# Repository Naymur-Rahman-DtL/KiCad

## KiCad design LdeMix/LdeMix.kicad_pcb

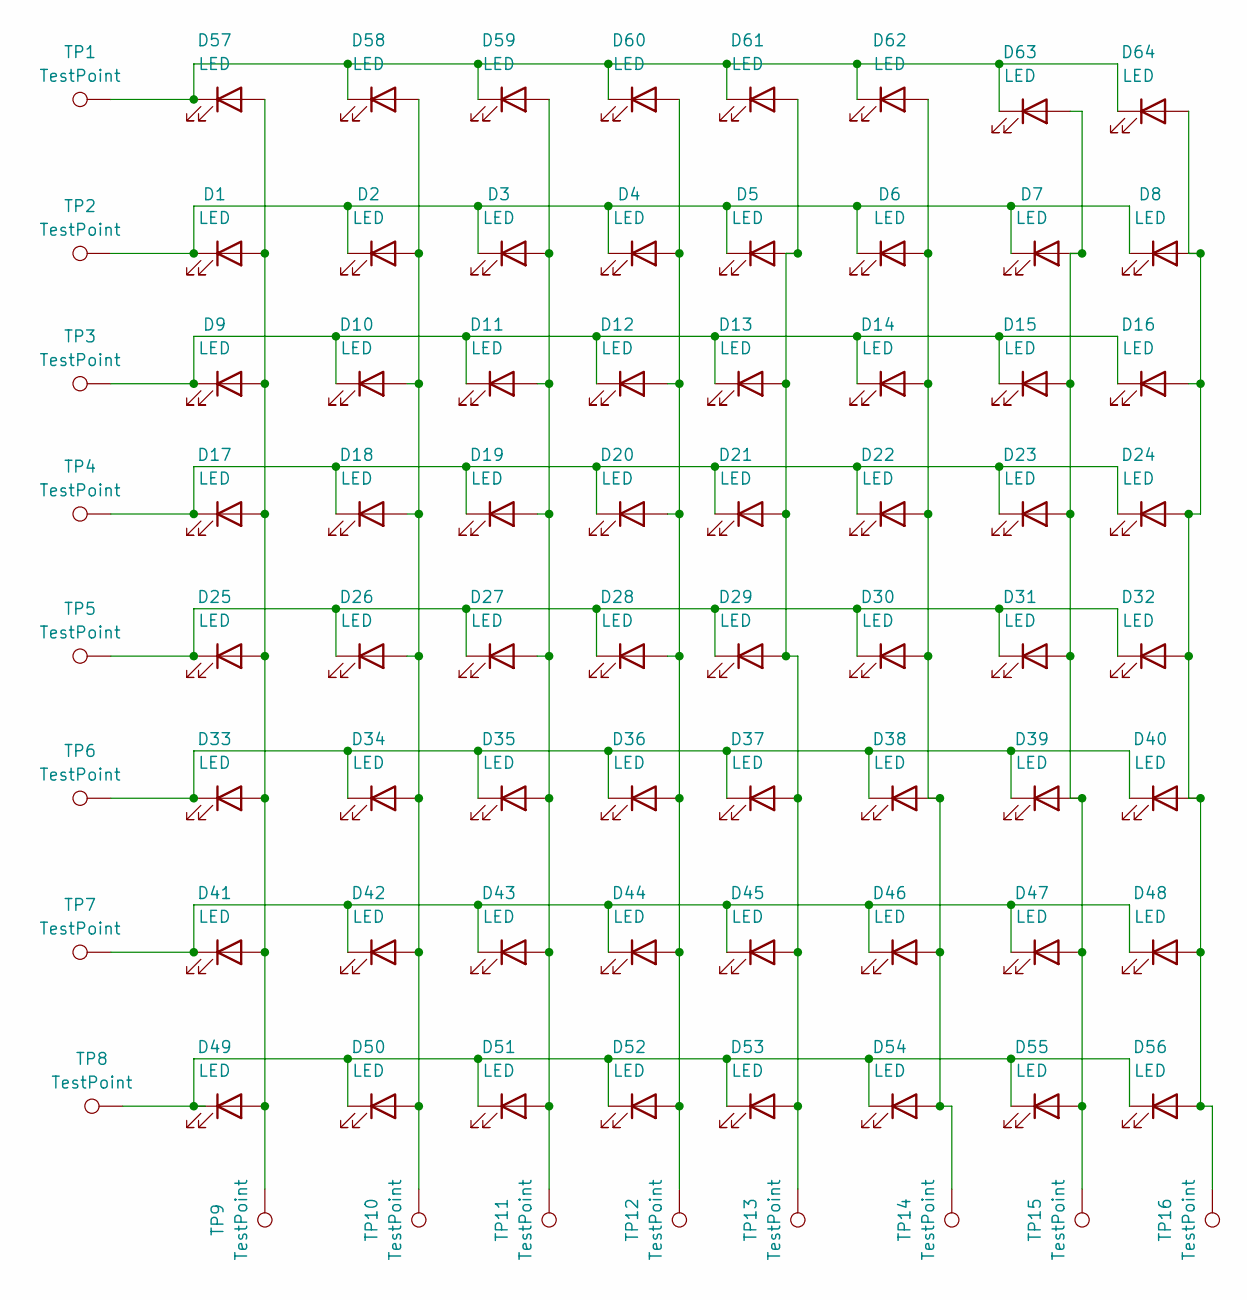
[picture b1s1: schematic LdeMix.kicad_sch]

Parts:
D1, D2, D3, D4, D5, D6, D7, D8, D9, D10, D11, D12, D13, D14, D15, D16, D17, D18, D19, D20, D21, D22, D23, D24, D25, D26, D27, D28, D29, D30, D31, D32, D33, D34, D35, D36, D37, D38, D39, D40, D41, D42, D43, D44, D45, D46, D47, D48, D49, D50, D51, D52, D53, D54, D55, D56, D57, D58, D59, D60, D61, D62, D63, D64: LED; LED_D3.0mm
TP1, TP2, TP3, TP4, TP5, TP6, TP7, TP8, TP9, TP10, TP11, TP12, TP13, TP14, TP15, TP16: TestPoint; Pin_D1.0mm_L10.0mm_LooseFit

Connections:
unnamed: D1.2 (A), D9.2 (A), D17.2 (A), D25.2 (A), D33.2 (A), D41.2 (A), D49.2 (A), D57.2 (A), TP9.1
unnamed: D1.1 (K), D2.1 (K), D3.1 (K), D4.1 (K), D5.1 (K), D6.1 (K), D7.1 (K), D8.1 (K), TP2.1
unnamed: D2.2 (A), D10.2 (A), D18.2 (A), D26.2 (A), D34.2 (A), D42.2 (A), D50.2 (A), D58.2 (A), TP10.1
unnamed: D9.1 (K), D10.1 (K), D11.1 (K), D12.1 (K), D13.1 (K), D14.1 (K), D15.1 (K), D16.1 (K), TP3.1
unnamed: D3.2 (A), D11.2 (A), D19.2 (A), D27.2 (A), D35.2 (A), D43.2 (A), D51.2 (A), D59.2 (A), TP11.1
unnamed: D4.2 (A), D12.2 (A), D20.2 (A), D28.2 (A), D36.2 (A), D44.2 (A), D52.2 (A), D60.2 (A), TP12.1
unnamed: D5.2 (A), D13.2 (A), D21.2 (A), D29.2 (A), D37.2 (A), D45.2 (A), D53.2 (A), D61.2 (A), TP13.1
unnamed: D6.2 (A), D14.2 (A), D22.2 (A), D30.2 (A), D38.2 (A), D46.2 (A), D54.2 (A), D62.2 (A), TP14.1
unnamed: D7.2 (A), D15.2 (A), D23.2 (A), D31.2 (A), D39.2 (A), D47.2 (A), D55.2 (A), D63.2 (A), TP15.1
unnamed: D8.2 (A), D16.2 (A), D24.2 (A), D32.2 (A), D40.2 (A), D48.2 (A), D56.2 (A), D64.2 (A), TP16.1
unnamed: D17.1 (K), D18.1 (K), D19.1 (K), D20.1 (K), D21.1 (K), D22.1 (K), D23.1 (K), D24.1 (K), TP4.1
unnamed: D25.1 (K), D26.1 (K), D27.1 (K), D28.1 (K), D29.1 (K), D30.1 (K), D31.1 (K), D32.1 (K), TP5.1
unnamed: D33.1 (K), D34.1 (K), D35.1 (K), D36.1 (K), D37.1 (K), D38.1 (K), D39.1 (K), D40.1 (K), TP6.1
unnamed: D41.1 (K), D42.1 (K), D43.1 (K), D44.1 (K), D45.1 (K), D46.1 (K), D47.1 (K), D48.1 (K), TP7.1
unnamed: D49.1 (K), D50.1 (K), D51.1 (K), D52.1 (K), D53.1 (K), D54.1 (K), D55.1 (K), D56.1 (K), TP8.1
unnamed: D57.1 (K), D58.1 (K), D59.1 (K), D60.1 (K), D61.1 (K), D62.1 (K), D63.1 (K), D64.1 (K), TP1.1

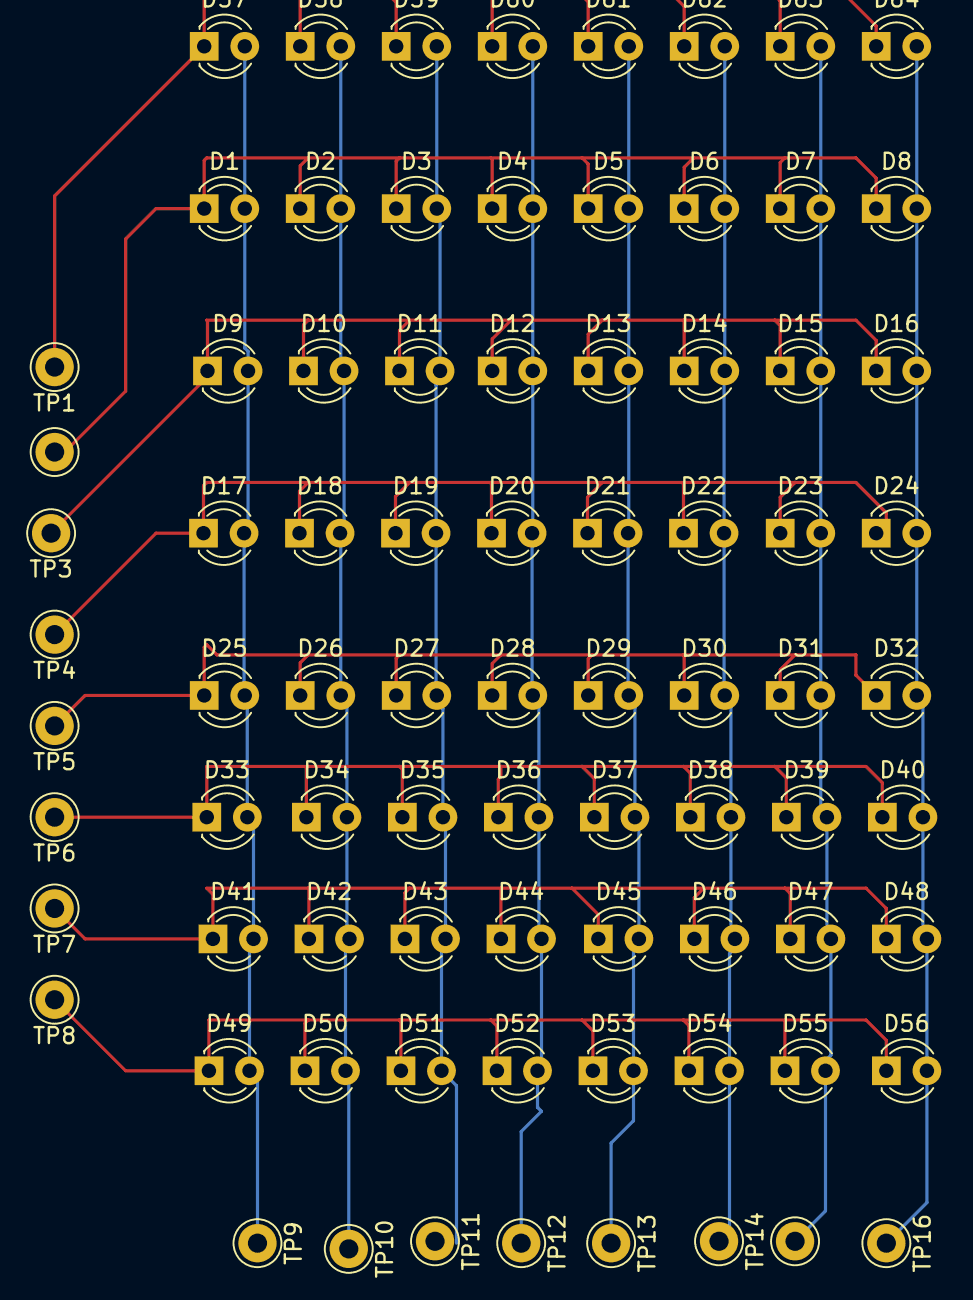
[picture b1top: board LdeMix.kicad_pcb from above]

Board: 2 copper layers, 80 parts (0 on the bottom side), 16 nets.

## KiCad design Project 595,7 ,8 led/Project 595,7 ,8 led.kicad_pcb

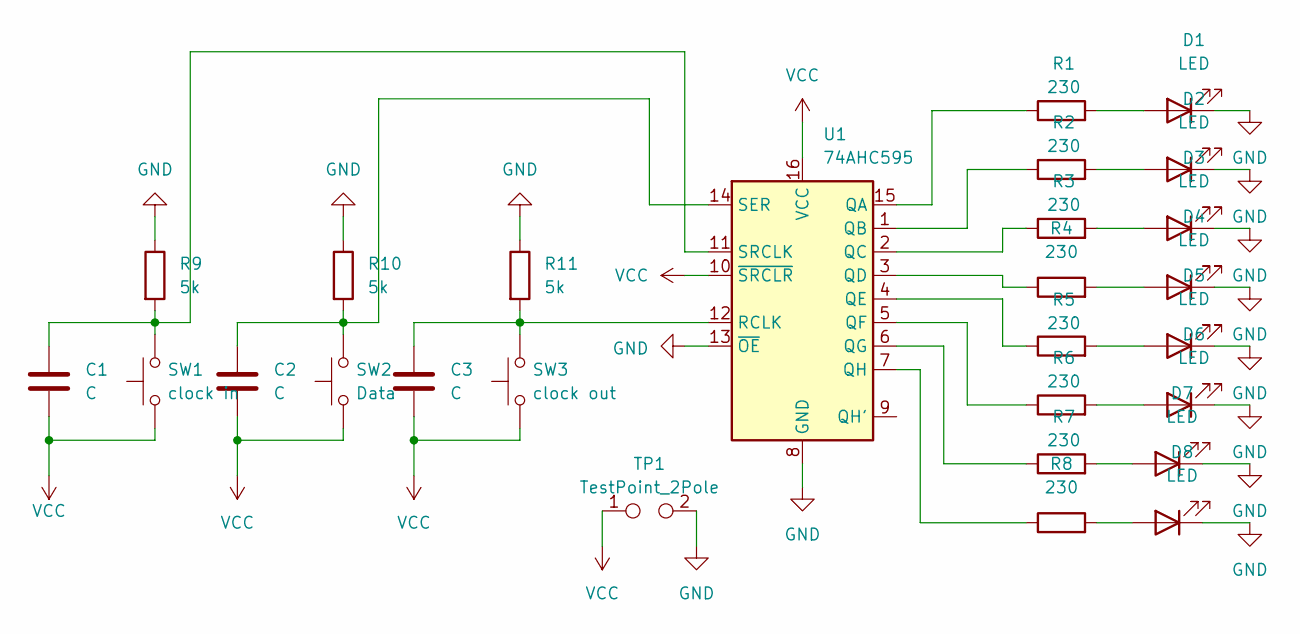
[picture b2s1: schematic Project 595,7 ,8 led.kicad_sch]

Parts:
C1, C2, C3: C; C_1206_3216Metric_Pad1.33x1.80mm_HandSolder
D1, D2, D3, D4, D5, D6, D7, D8: LED; LED_D3.0mm
R1, R2, R3, R4, R5, R6, R7, R8: 230; R_0815_2038Metric_Pad1.20x4.05mm_HandSolder
R9, R10, R11: 5k; R_0815_2038Metric_Pad1.20x4.05mm_HandSolder
SW1: clock in; SW_PUSH_6mm
SW2: Data; SW_PUSH_6mm
SW3: clock out; SW_PUSH_6mm
TP1: TestPoint_2Pole; Stocko_MKS_1651-6-0-202_1x2_P2.50mm_Vertical
U1: 74AHC595; CERDIP-16_W7.62mm_SideBrazed

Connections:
GND: D1.1 (K), D2.1 (K), D3.1 (K), D4.1 (K), D5.1 (K), D6.1 (K), D7.1 (K), D8.1 (K), R9.1, R10.1, R11.1, TP1.2, U1.8 (GND), U1.13 (~OE)
unnamed: D1.2 (A), R1.2
unnamed: D2.2 (A), R2.2
unnamed: D3.2 (A), R3.2
unnamed: D4.2 (A), R4.2
unnamed: D5.2 (A), R5.2
unnamed: D6.2 (A), R6.2
unnamed: D7.2 (A), R7.2
unnamed: D8.2 (A), R8.2
unnamed: R1.1, U1.15 (QA)
unnamed: R2.1, U1.1 (QB)
unnamed: R3.1, U1.2 (QC)
unnamed: R4.1, U1.3 (QD)
unnamed: R5.1, U1.4 (QE)
unnamed: R6.1, U1.5 (QF)
unnamed: R7.1, U1.6 (QG)
unnamed: R8.1, U1.7 (QH)
unnamed: C3.1, R11.2, SW3.2, U1.12 (RCLK)
unnamed: C2.1, R10.2, SW2.2, U1.14 (SER)
unnamed: C1.1, R9.2, SW1.2, U1.11 (SRCLK)
VCC: C1.2, C2.2, C3.2, SW1.1, SW2.1, SW3.1, TP1.1, U1.10 (~SRCLR), U1.16 (VCC)

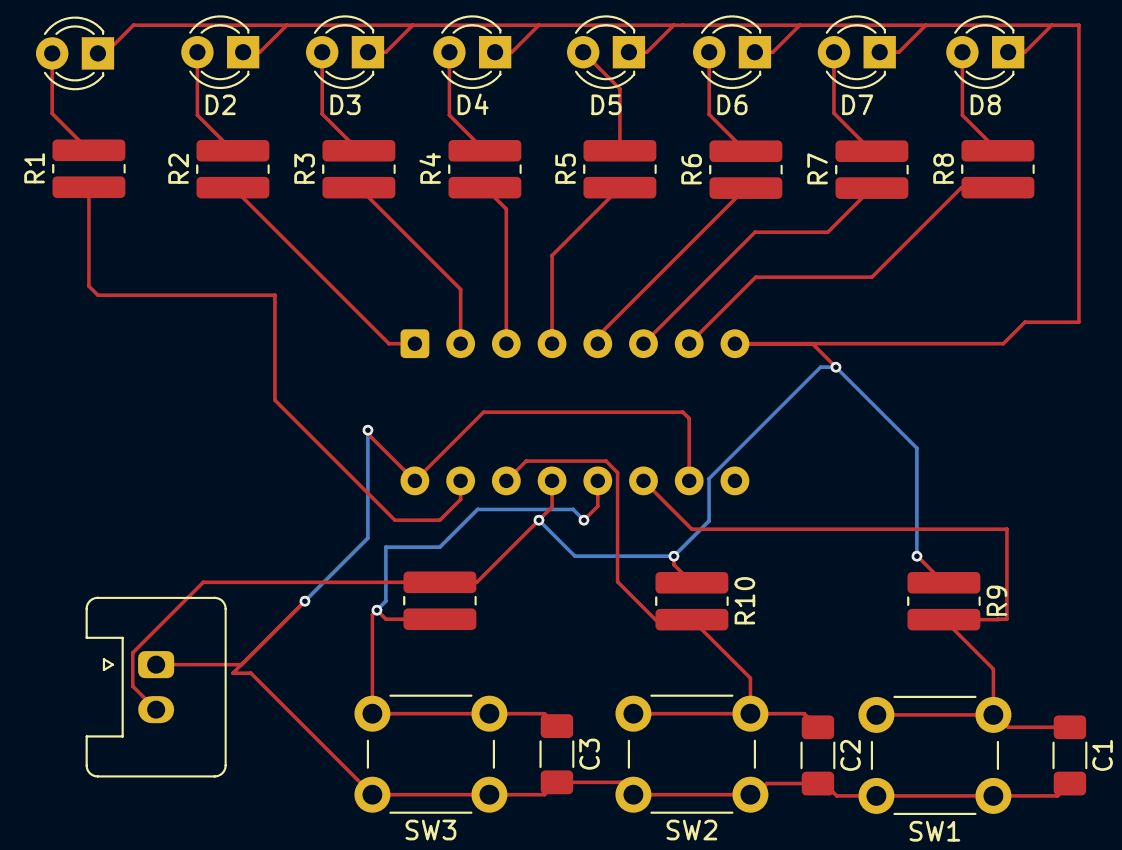
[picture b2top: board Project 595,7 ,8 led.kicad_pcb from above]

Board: 2 copper layers, 27 parts (1 on the bottom side), 21 nets.

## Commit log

2025-07-28 Project 595,7 ,8 led
    add file
2025-07-29 LdeMix
    add file
